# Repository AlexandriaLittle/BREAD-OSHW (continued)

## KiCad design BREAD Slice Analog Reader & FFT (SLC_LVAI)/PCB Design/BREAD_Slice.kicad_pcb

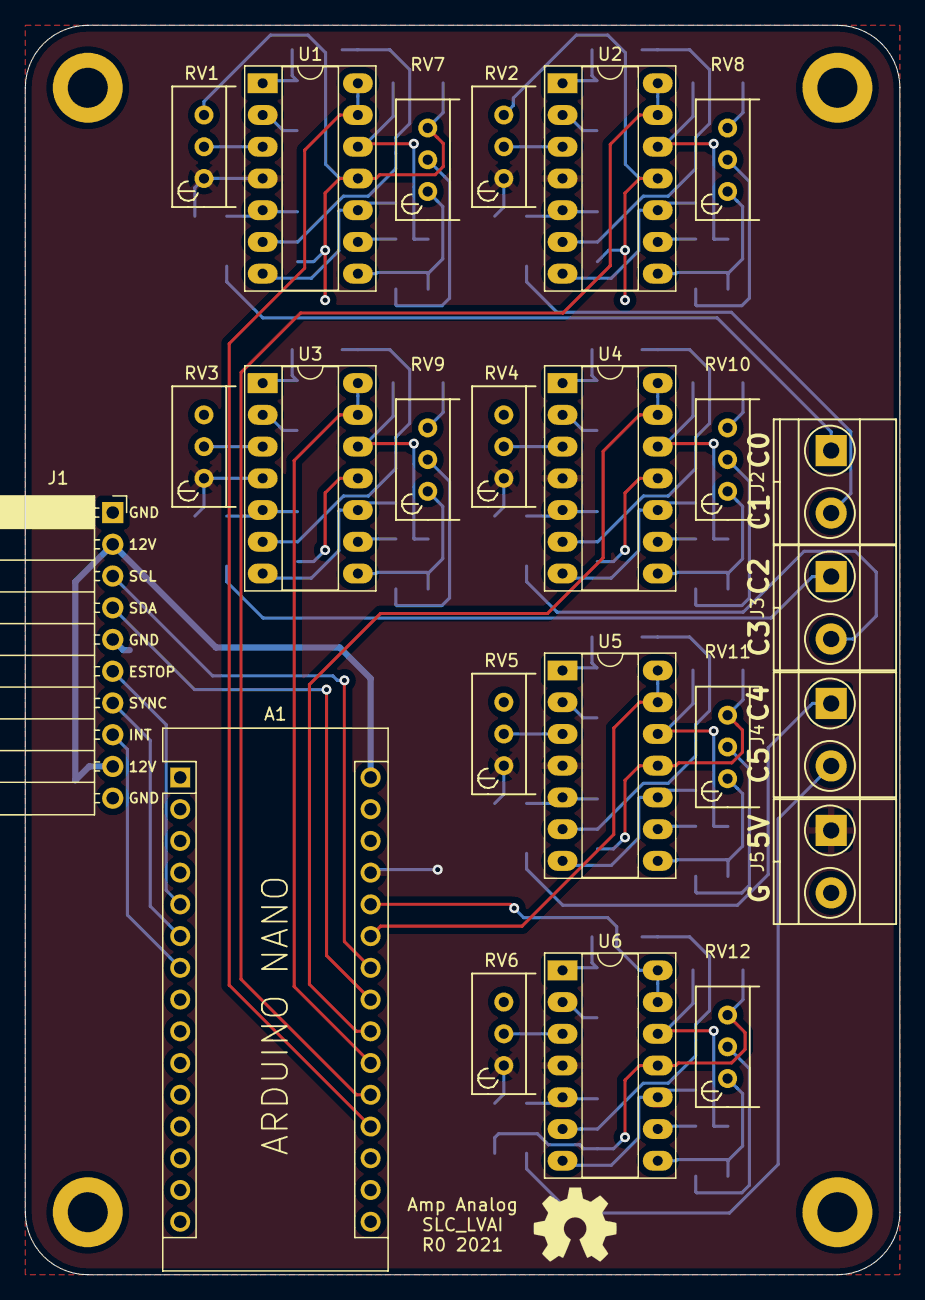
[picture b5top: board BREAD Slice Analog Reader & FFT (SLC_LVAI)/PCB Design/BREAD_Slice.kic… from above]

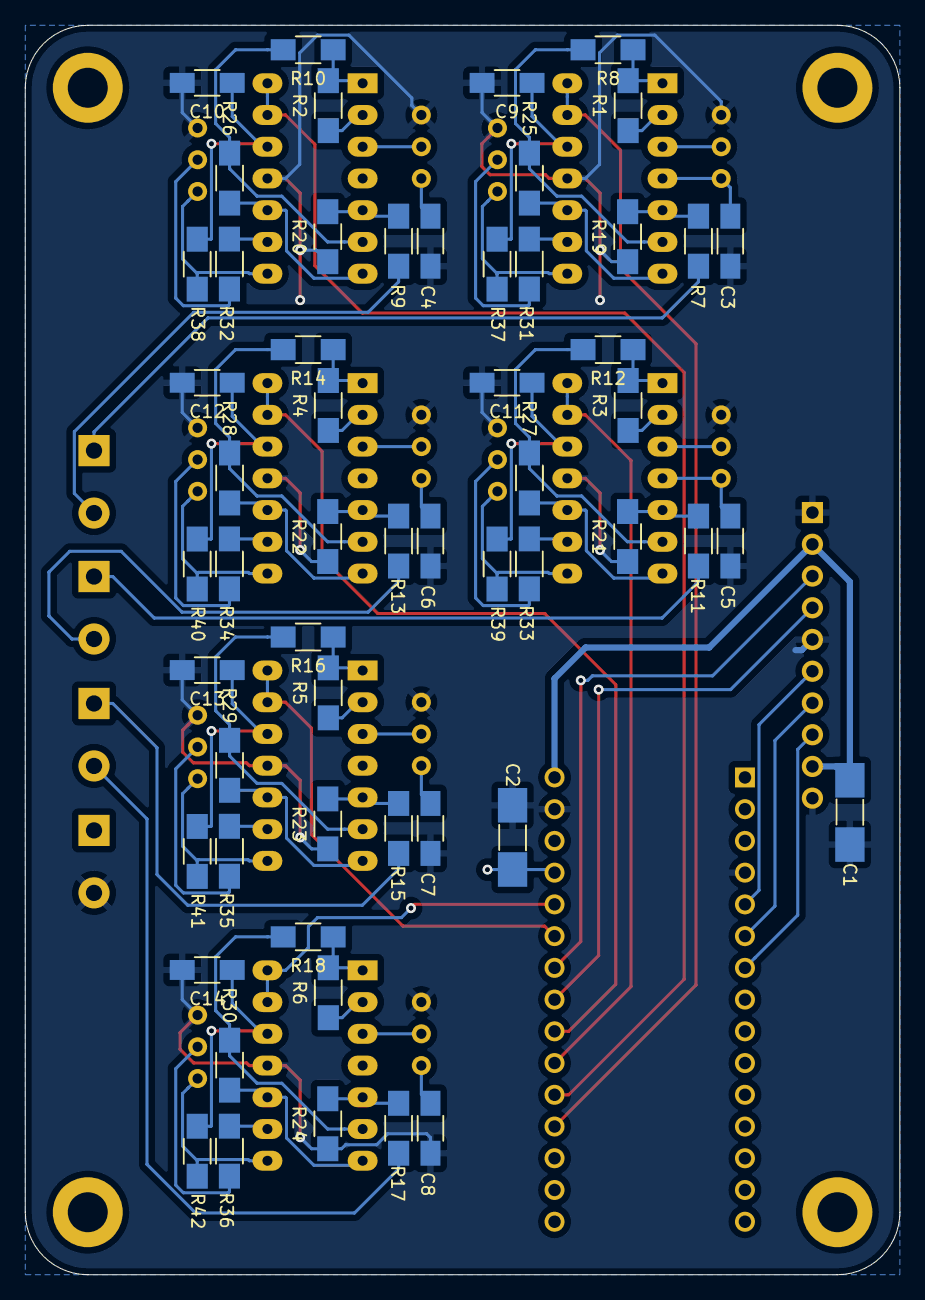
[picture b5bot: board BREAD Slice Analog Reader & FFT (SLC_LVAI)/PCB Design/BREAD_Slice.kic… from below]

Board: 2 copper layers, 70.0 x 100.0 mm, 85 parts (56 on the bottom side), 80 nets.

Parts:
A1: Arduino_Nano_v3.x; Arduino_Nano
C1, C2: 10uF_t; C_2312
C3, C4, C5, C6, C7, C8, C9, C10, C11, C12, C13, C14: 1uF_t; C_1206_HandSoldering
H1, H2, H3, H4: MountingHole; MountingHole_3.2mm_M3_DIN965_Pad
J1: Conn_01x10_Female; PinSocket_1x10_P2.54mm_Horizontal
J2, J3, J4, J5: Term_2; TerminalBlock_Pheonix_MKDS1.5-2pol
Logo1: Logo_Open_Hardware_Small; OSHW-Symbol_6.7x6mm_SilkScreen
R1, R2, R3, R4, R5, R6, R7, R8, R9, R10, R11, R12, R13, R14, R15, R16, R17, R18, R19, R20, R21, R22, R23, R24, R25, R26, R27, R28, R29, R30, R31, R32, R33, R34, R35, R36, R37, R38, R39, R40, R41, R42: 1K; R_1206_HandSoldering
RV1, RV2, RV3, RV4, RV5, RV6, RV7, RV8, RV9, RV10, RV11, RV12: 10k_t; Potentiometer_Bourns_3296W_3-8Zoll_Inline_ScrewUp
U1, U2, U3, U4, U5, U6: MCP6004; DIP-14_W7.62mm_Socket_LongPads

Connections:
+5V: A1.27, C2.1, C3.1, C4.1, C5.1, C6.1, C7.1, C8.1, J5.1, RV1.1, RV2.1, RV3.1, RV4.1, RV5.1, RV6.1, U1.4, U2.4, U3.4, U4.4, U5.4, U6.4
+12V: A1.30, C1.1, J1.2, J1.9
/CH0_AI: A1.19, U1.13, U1.14
/CH1_AI: A1.20, U2.13, U2.14
/CH2_AI: A1.21, U3.13, U3.14
/CH3_AI: A1.22, U4.13, U4.14
/CH4_AI: A1.25, U5.13, U5.14
/CH5_AI: A1.26, U6.13, U6.14
/Ch0_in: J2.1, R7.1
/Ch1_in: J2.2, R9.1
/Ch2_in: J3.1, R11.1
/Ch3_in: J3.2, R13.1
/Ch4_in: J4.1, R15.1
/Ch5_in: J4.2, R17.1
/E_STOP: A1.5, J1.6
/I2C_CLK: A1.24, J1.3
/I2C_DAT: A1.23, J1.4
/INT: A1.7, J1.8
/SYNC: A1.6, J1.7
GND: A1.4, A1.29, C1.2, C2.2, C3.2, C4.2, C5.2, C6.2, C7.2, C8.2, C9.2, C10.2, C11.2, C12.2, C13.2, C14.2, J1.1, J1.5, J1.10, J5.2, R19.1, R20.1, R21.1, R22.1, R23.1, R24.1, RV1.3, RV2.3, RV3.3, RV4.3, RV5.3, RV6.3, RV7.3, RV8.3, RV9.3, RV10.3, RV11.3, RV12.3, U1.11, U2.11, U3.11, U4.11, U5.11, U6.11
unnamed: C9.1, R37.2, U1.12
unnamed: C10.1, R38.2, U2.12
unnamed: C11.1, R39.2, U3.12
unnamed: C12.1, R40.2, U4.12
unnamed: C13.1, R41.2, U5.12
unnamed: C14.1, R42.2, U6.12
unnamed: R1.1, U1.2
unnamed: R1.2, R8.1, U1.1
unnamed: R2.1, U2.2
unnamed: R3.1, U3.2
unnamed: R4.1, U4.2
unnamed: R5.1, U5.2
unnamed: R6.1, U6.2
unnamed: R2.2, R10.1, U2.1
unnamed: R10.2, R26.1, U2.6
unnamed: R11.2, R21.2, U3.5
unnamed: R3.2, R12.1, U3.1
unnamed: R12.2, R27.1, U3.6
unnamed: R13.2, R22.2, U4.5
unnamed: R4.2, R14.1, U4.1
unnamed: R14.2, R28.1, U4.6
unnamed: R15.2, R23.2, U5.5
unnamed: R5.2, R16.1, U5.1
unnamed: R16.2, R29.1, U5.6
unnamed: R17.2, R24.2, U6.5
unnamed: R6.2, R18.1, U6.1
unnamed: R18.2, R30.1, U6.6
unnamed: R7.2, R19.2, U1.5
unnamed: R9.2, R20.2, U2.5
unnamed: R8.2, R25.1, U1.6
unnamed: R25.2, U1.7, U1.10
unnamed: R26.2, U2.7, U2.10
unnamed: R27.2, U3.7, U3.10
unnamed: R28.2, U4.7, U4.10
unnamed: R29.2, U5.7, U5.10
unnamed: R30.2, U6.7, U6.10
unnamed: R31.1, U1.9
unnamed: R31.2, RV7.2
unnamed: R32.1, U2.9
unnamed: R32.2, RV8.2
unnamed: R33.1, U3.9
unnamed: R33.2, RV9.2
unnamed: R34.1, U4.9
unnamed: R34.2, RV10.2
unnamed: R35.1, U5.9
unnamed: R35.2, RV11.2
unnamed: R36.1, U6.9
unnamed: R36.2, RV12.2
unnamed: R37.1, RV7.1, U1.8
unnamed: R38.1, RV8.1, U2.8
unnamed: R39.1, RV9.1, U3.8
unnamed: R40.1, RV10.1, U4.8
unnamed: R41.1, RV11.1, U5.8
unnamed: R42.1, RV12.1, U6.8
unnamed: RV1.2, U1.3
unnamed: RV2.2, U2.3
unnamed: RV3.2, U3.3
unnamed: RV4.2, U4.3
unnamed: RV5.2, U5.3
unnamed: RV6.2, U6.3

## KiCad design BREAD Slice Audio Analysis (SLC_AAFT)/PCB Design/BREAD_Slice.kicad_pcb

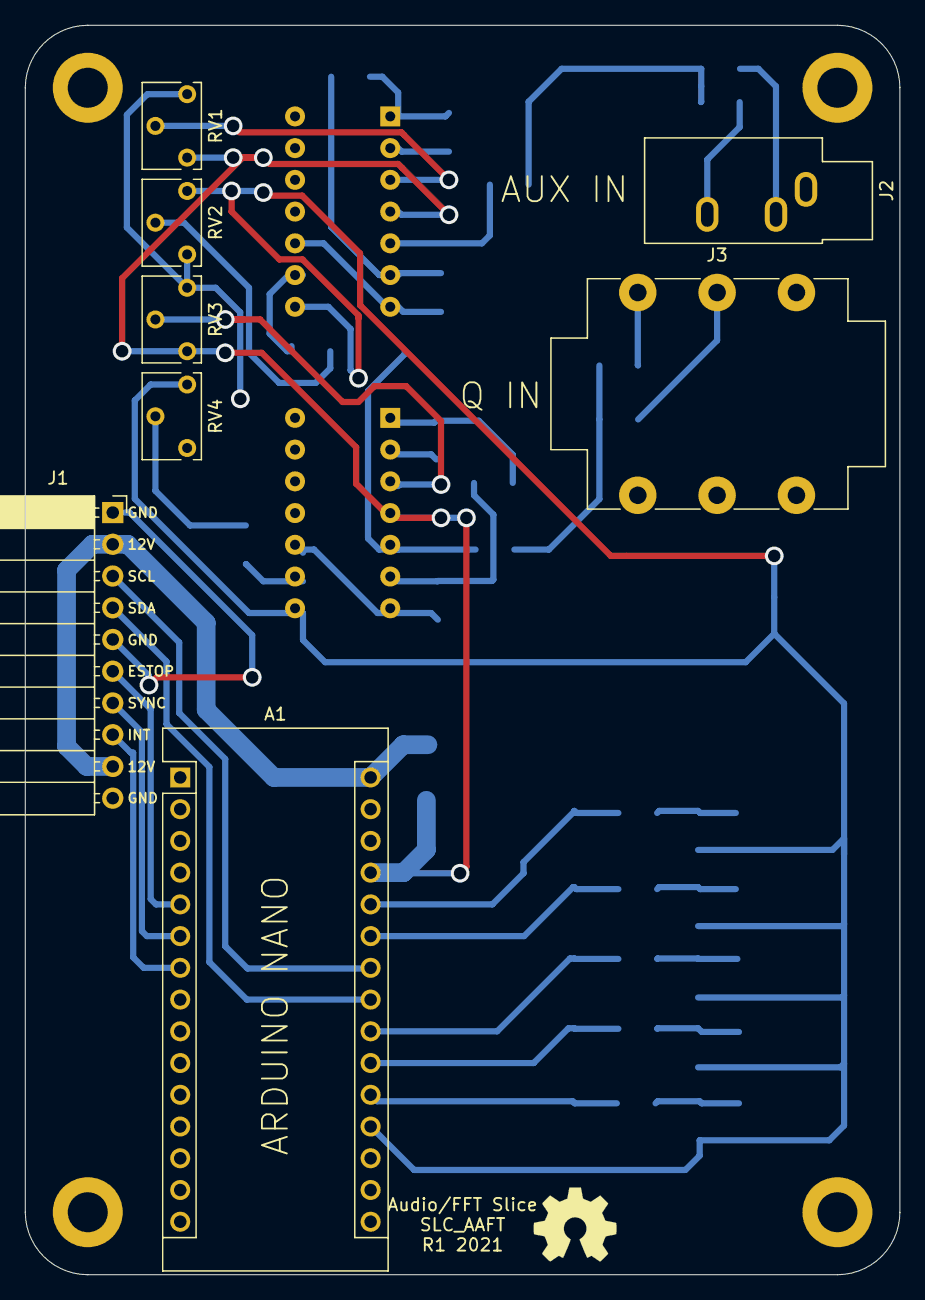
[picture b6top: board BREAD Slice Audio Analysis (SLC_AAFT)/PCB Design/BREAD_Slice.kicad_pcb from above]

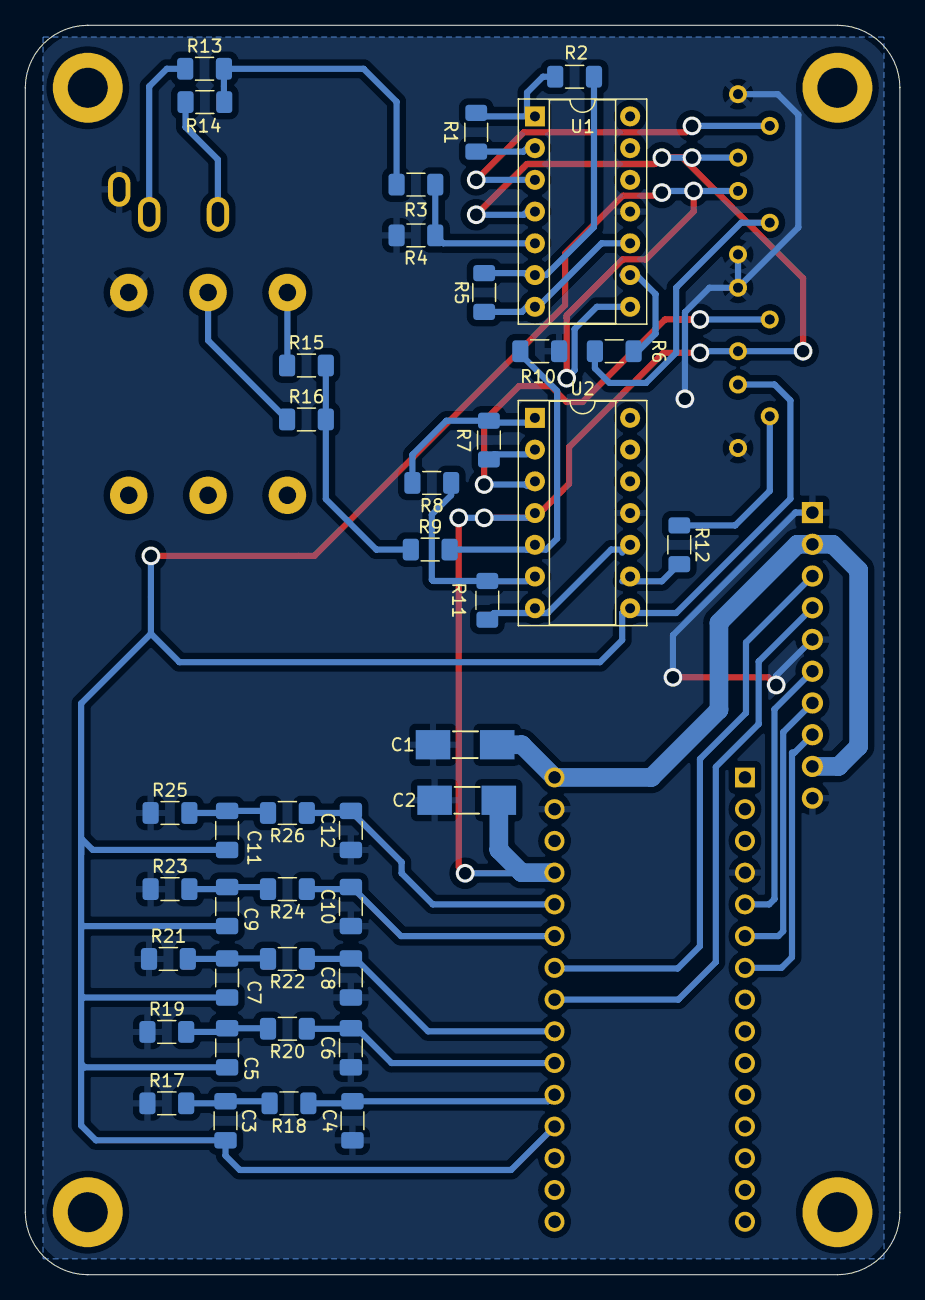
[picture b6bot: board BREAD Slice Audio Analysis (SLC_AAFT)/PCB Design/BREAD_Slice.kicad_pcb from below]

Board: 2 copper layers, 70.0 x 100.0 mm, 53 parts (40 on the bottom side), 41 nets.

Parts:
A1: Arduino_Nano_v3.x; Arduino_Nano
C1, C2: 10uF_t; C_2312
C3: 10 uF; C_1206_3216Metric_Pad1.33x1.80mm_HandSolder
C4, C5, C6, C7, C8, C9, C10, C11, C12: 0.1 uF; C_1206_3216Metric_Pad1.33x1.80mm_HandSolder
H1, H2, H3, H4: MountingHole; MountingHole_3.2mm_M3_DIN965_Pad
J1: Conn_01x10_Female; PinSocket_1x10_P2.54mm_Horizontal
J2: Aux; Jack_3.5mm_CUI_SJ1-3533NG_Horizontal
J3: Q_Inch; Jack_6.35mm_Neutrik_NMJ6HCD2_Horizontal
Logo1: Logo_Open_Hardware_Small; OSHW-Symbol_6.7x6mm_SilkScreen
R1, R2, R3, R4, R5, R6, R7, R8, R9, R10, R11, R12: 1k; R_1206_3216Metric_Pad1.30x1.75mm_HandSolder
R13, R14, R15, R16: 500; R_1206_3216Metric_Pad1.30x1.75mm_HandSolder
R17: 400; R_1206_3216Metric_Pad1.30x1.75mm_HandSolder
R18, R19: 1.8 k; R_1206_3216Metric_Pad1.30x1.75mm_HandSolder
R20, R21: 900; R_1206_3216Metric_Pad1.30x1.75mm_HandSolder
R22, R23: 600; R_1206_3216Metric_Pad1.30x1.75mm_HandSolder
R24, R25: 450; R_1206_3216Metric_Pad1.30x1.75mm_HandSolder
R26: 360; R_1206_3216Metric_Pad1.30x1.75mm_HandSolder
RV1, RV2, RV3, RV4: 10k; Potentiometer_Bourns_3266W_Vertical
U1, U2: MCP6004; DIP-14_W7.62mm_Socket

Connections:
+5V: A1.27, C2.1, RV1.1, RV3.1, U1.4, U2.4
+12V: A1.30, C1.1, J1.2, J1.9
/AUX_IN: R3.1, R13.2, R14.2
/AUX_SW: A1.19, C3.2, C5.2, C7.2, C9.2, C11.2, RV2.3, RV4.3, U1.8, U2.8
/E_STOP: A1.5, J1.6
/HIGH: A1.26, C12.2, R26.1
/HIGH_MID: A1.25, C10.2, R24.1
/I2C_CLK: A1.24, J1.3
/I2C_DAT: A1.23, J1.4
/INT: A1.6, J1.7
/LOW: A1.20, C4.2, R18.1
/LOW_MID: A1.21, C6.2, R20.1
/MID: A1.22, C8.2, R22.1
/Q_IN: R9.1, R15.2, R16.2
/SYNC: A1.7, J1.8
GND: A1.4, A1.29, C1.2, C2.2, C4.1, C6.1, C8.1, C10.1, C12.1, J1.1, J1.5, J1.10, J2.S, J3.S, R4.2, R10.2, R17.1, R19.1, R21.1, R23.1, R25.1, RV1.3, RV2.1, RV3.3, RV4.1, U1.11, U2.11
unnamed: C3.1, R17.2, R18.2
unnamed: C5.1, R19.2, R20.2
unnamed: C7.1, R21.2, R22.2
unnamed: C9.1, R23.2, R24.2
unnamed: C11.1, R25.2, R26.2
unnamed: J2.R, R14.1
unnamed: J2.T, R13.1
unnamed: J3.R, R16.1
unnamed: J3.T, R15.1
unnamed: R1.1, R2.2, U1.1
unnamed: R1.2, U1.2
unnamed: R2.1, R5.2, U1.6
unnamed: R3.2, R4.1, U1.5
unnamed: R5.1, U1.7, U1.10
unnamed: R6.1, RV2.2
unnamed: R6.2, U1.9
unnamed: R7.1, R8.2, U2.1
unnamed: R7.2, U2.2
unnamed: R9.2, R10.1, U2.5
unnamed: R11.1, U2.7, U2.10
unnamed: R8.1, R11.2, U2.6
unnamed: R12.1, RV4.2
unnamed: R12.2, U2.9
unnamed: RV1.2, U1.3
unnamed: RV3.2, U2.3

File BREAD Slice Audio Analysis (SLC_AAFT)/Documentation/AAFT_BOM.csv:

Id,Designator,Package,Quantity,Designation,Supplier and ref
1,"U2,U1",DIP-14_W7.62mm_SMDSocket_SmallPads,2,MCP6004,
2,J2,Jack_3.5mm_CUI_SJ1-3533NG_Horizontal,1,Aux,
3,"RV4,RV3,RV2,RV1",Potentiometer_Bourns_3266W_Vertical,4,10k,
4,R26,R_1206_3216Metric_Pad1.30x1.75mm_HandSolder,1,360,
5,"R25,R24",R_1206_3216Metric_Pad1.30x1.75mm_HandSolder,2,450,
6,"R23,R22",R_1206_3216Metric_Pad1.30x1.75mm_HandSolder,2,600,
7,"R21,R20",R_1206_3216Metric_Pad1.30x1.75mm_HandSolder,2,900,
8,"R19,R18",R_1206_3216Metric_Pad1.30x1.75mm_HandSolder,2,1.8 k,
9,R17,R_1206_3216Metric_Pad1.30x1.75mm_HandSolder,1,400,
10,"R16,R15,R14,R13",R_1206_3216Metric_Pad1.30x1.75mm_HandSolder,4,500,
11,"R12,R11,R10,R9,R8,R7,R6,R5,R4,R3,R2,R1",R_1206_3216Metric_Pad1.30x1.75mm_HandSolder,12,1k,
12,J3,Jack_6.35mm_Neutrik_NMJ6HCD2_Horizontal,1,Q_Inch,
13,"C12,C11,C10,C9,C8,C7,C6,C5,C4",C_1206_3216Metric_Pad1.33x1.80mm_HandSolder,9,0.1 uF,
14,C3,C_1206_3216Metric_Pad1.33x1.80mm_HandSolder,1,10 uF,
15,Logo1,OSHW-Symbol_6.7x6mm_SilkScreen,1,Logo_Open_Hardware_Small,
16,"H4,H3,H2,H1",MountingHole_3.2mm_M3_DIN965_Pad,4,MountingHole,
17,"C1,C2",C_2312,2,10uF_t,
18,A1,Arduino_Nano,1,Arduino_Nano_v3.x,
19,J1,PinSocket_1x10_P2.54mm_Horizontal,1,Conn_01x10_Female,
